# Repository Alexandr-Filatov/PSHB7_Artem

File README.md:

# C6_Driver_3
Driver board for C6 IGBT Module.

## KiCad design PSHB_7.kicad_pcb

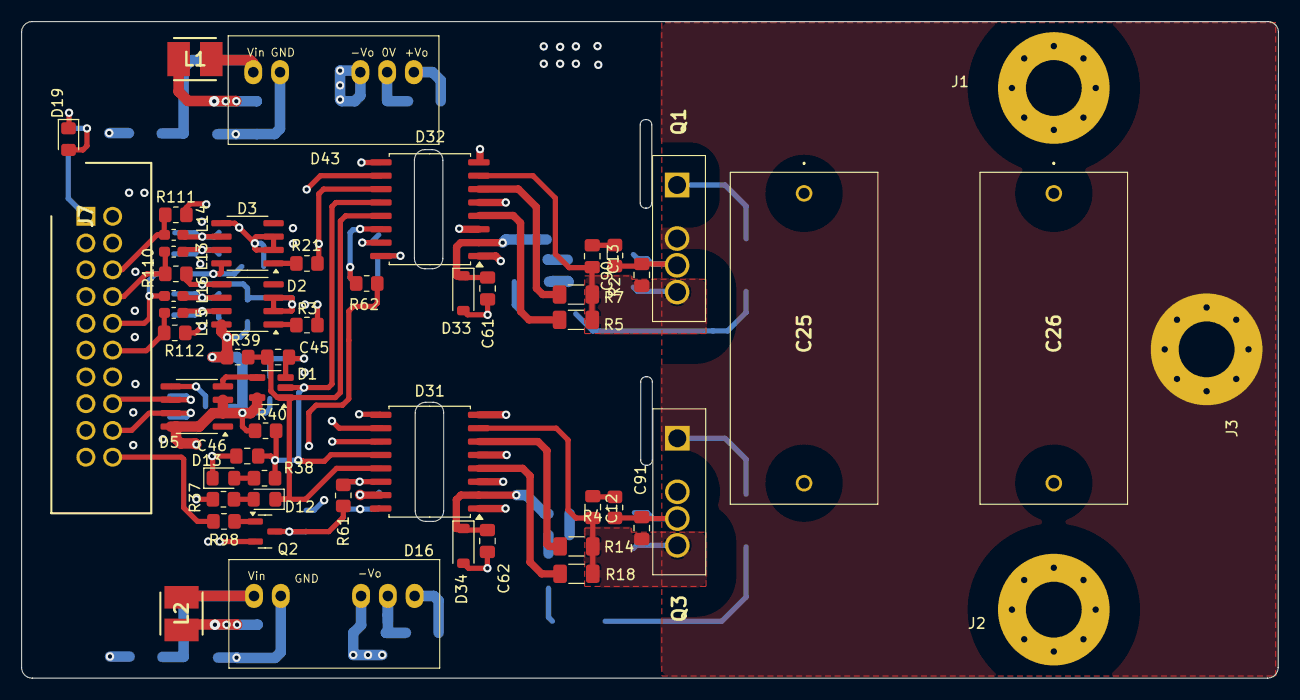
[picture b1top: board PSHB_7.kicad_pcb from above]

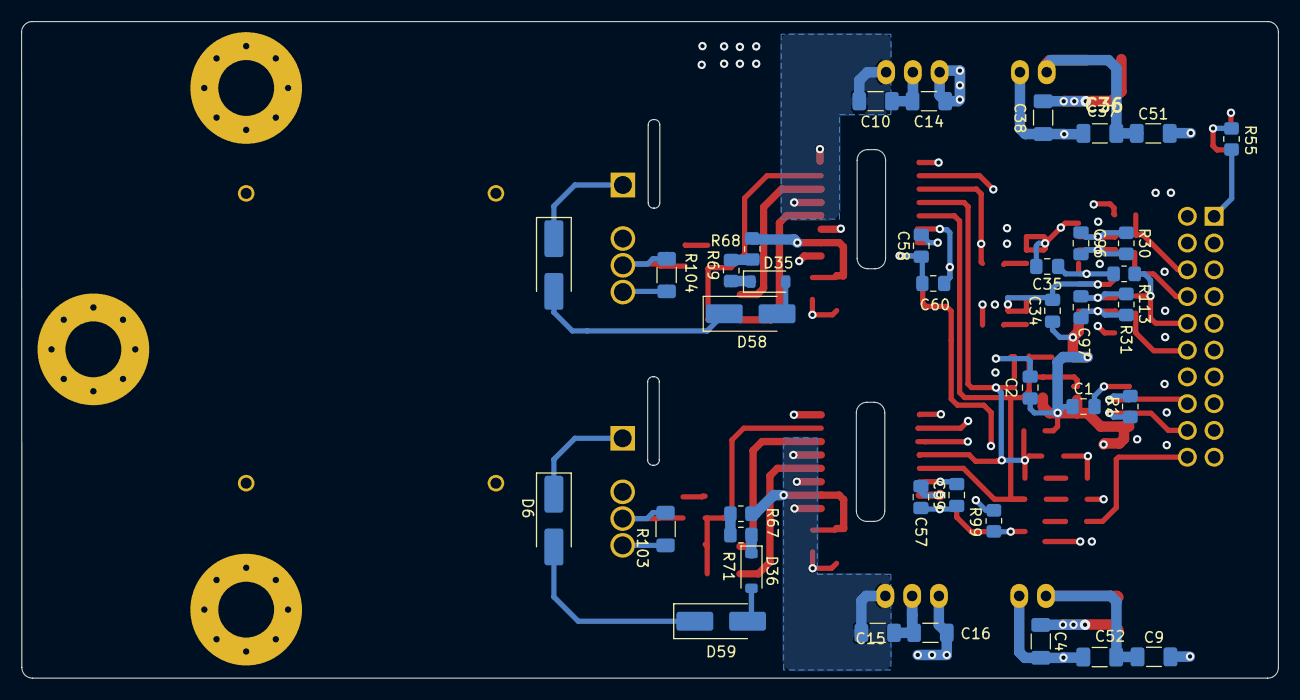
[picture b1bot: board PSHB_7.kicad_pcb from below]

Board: 6 copper layers, 119.3 x 62.3 mm, 92 parts (38 on the bottom side), 55 nets.

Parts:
C1, C2, C34, C35: 2.2u; C_0805_2012Metric_Pad1.18x1.45mm_HandSolder
C4, C9, C37, C38: 4.7u; C_1206_3216Metric_Pad1.33x1.80mm_HandSolder
C10, C14, C15, C16: 10uf; R_1206_3216Metric_Pad1.30x1.75mm_HandSolder
C12, C13: 470p; C_0805_2012Metric_Pad1.18x1.45mm_HandSolder
C25, C26: B32774D8505K000
C45, C46, C96, C97: 56p; C_0805_2012Metric_Pad1.18x1.45mm_HandSolder
C51, C52: 100p; C_1206_3216Metric_Pad1.33x1.80mm_HandSolder
C57, C58: 0.1u; C_0805_2012Metric_Pad1.18x1.45mm_HandSolder
C59, C60: 1000p; C_0805_2012Metric_Pad1.18x1.45mm_HandSolder
C61, C62: 220p; C_0805_2012Metric_Pad1.18x1.45mm_HandSolder
C90, C91: C_0805_2012Metric_Pad1.18x1.45mm_HandSolder
D1: SOT-23-5_HandSoldering
D2, D3, D5: SOIC-8_3.9x4.9mm_P1.27mm
D4, D6, D58, D59: D_SMA_Handsoldering
D12, D13, D19: LED_0805_2012Metric_Pad1.15x1.40mm_HandSolder
D16, D43: QA
D31, D32: SOIC-16W_7.5x10.3mm_P1.27mm
D33, D34, D35, D36: D_SOD-123
J1, J2, J3: MountingHole_5.3mm_M5_Pad_Via
J7: DS1013-20SSIB1-B-0; SHDR20W69P254X254_2X10_3300X910X955P
L1, L2: IFSC1515AHER220M01; INDM4040X190N
L13, L14, L15, L16: 1u; L_0603_1608Metric_Pad1.05x0.95mm_HandSolder
Q1, Q3: C3M0065100K; E4M0013120K
Q2: SOT-23
R1, R30, R31, R61, R62: 120; R_0805_2012Metric_Pad1.20x1.40mm_HandSolder
R2, R4, R37, R38, R39, R40, R99: 1k; R_0805_2012Metric_Pad1.20x1.40mm_HandSolder
R3, R21, R69, R71: 0; R_0805_2012Metric_Pad1.20x1.40mm_HandSolder
R5, R18: 6.8; R_1206_3216Metric_Pad1.30x1.75mm_HandSolder
R7, R14: 10; R_1206_3216Metric_Pad1.30x1.75mm_HandSolder
R55: 3k; R_0805_2012Metric_Pad1.20x1.40mm_HandSolder
R67, R68: 220; R_0805_2012Metric_Pad1.20x1.40mm_HandSolder
R98: 4.7k; R_0805_2012Metric_Pad1.20x1.40mm_HandSolder
R103, R104: 10k; R_1206_3216Metric_Pad1.30x1.75mm_HandSolder
R110, R111, R112, R113: 560; R_0805_2012Metric_Pad1.20x1.40mm_HandSolder

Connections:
+5V: C1.1, C2.1, C34.1, C35.1, C57.2, C58.2, D1.5 (Vcc), D2.8 (VCC), D3.8 (VCC), D5.2 (RE), D5.3 (DE), D5.8 (VCC), D31.15 (Vcc1), D32.15 (Vcc1), J7.4, J7.14, R37.2, R39.2, R40.2, R99.2, R111.2, R113.2
+15V: C4.1, C38.1, J7.1, L1.1, L2.1, R55.2
+15V_H1: C10.1, D32.5 (Vcc2), D43.7 (+Vo)
+15V_L1: C15.1, D16.7 (+Vo), D31.5 (Vcc2)
-4V_H1: C14.2, D32.1 (Vee2), D32.8 (Vee2), D43.5 (-Vo)
-4V_L1: C16.2, D16.5 (-Vo), D31.1 (Vee2), D31.8 (Vee2)
D1: C25.1, C26.1, D4.1 (K), J1.1 (Pin_1_1), Q1.1 (D)
D2: C10.2, C14.1, C61.2, C90.1, D6.1 (K), D32.3 (GND2), D33.2 (A), D43.6 (0V), J3.1 (Pin_1_1), Q1.2 (S), Q1.3 (DS), Q3.1 (D), R2.1, R104.1
DS2: C15.2, C16.1, C25.2, C26.2, C62.2, C91.1, D16.6 (0V), D31.3 (GND2), D34.2 (A), J2.1 (Pin_1_1), Q3.2 (S), Q3.3 (DS), R4.1, R103.1
ERR_A_N: D5.7 (B), J7.18, R1.1
ERR_A_P: D5.6 (A), J7.16, R1.2
FLT_A: C45.1, D1.1 (B), D12.1 (K), D31.13 (~FLT), D32.13 (~FLT), R39.1
G1: C13.1, C90.2, D32.7 (CLAMP), Q1.4 (G), R5.1, R7.2, R104.2
G2: C12.1, C91.2, D31.7 (CLAMP), Q3.4 (G), R14.2, R18.1, R103.2
GND: C1.2, C2.2, C4.2, C9.2, C34.2, C35.2, C37.2, C38.2, C45.2, C46.2, C51.2, C52.2, C57.1, C58.1, C59.1, C60.1, D1.3 (GND), D2.2 (RE), D2.3 (DE), D2.5 (GND), D3.2 (RE), D3.3 (DE), D3.5 (GND), D5.5 (GND), D13.1 (K), D16.2 (GND), D19.1 (K), D31.9 (GND1), D31.16 (TEST), D32.9 (GND1), D32.16 (TEST), D43.2 (GND), J7.2, J7.3, J7.5, J7.7, J7.9, J7.11, J7.13, J7.15, J7.17, J7.19, Q2.2 (E), R110.1, R112.1
IN-_HS: D31.10 (IN+), D32.11 (IN-), R21.2
IN-_LS: D31.11 (IN-), D32.10 (IN+), R3.2
unnamed: C12.2, R4.2
unnamed: C13.2, R2.2
unnamed: D1.4 (Y), D5.4 (DI)
unnamed: C97.1, D2.6 (A), L16.1, R31.2
unnamed: C97.2, D2.7 (B), L15.2, R31.1
unnamed: C96.1, D3.6 (A), L14.1, R30.2
unnamed: C96.2, D3.7 (B), L13.2, R30.1
unnamed: D4.2 (A), D58.1 (K)
unnamed: D12.2 (A), R37.1
unnamed: D13.2 (A), R38.1
unnamed: C9.1, C52.1, D16.1 (Vin), L2.2
unnamed: D19.2 (A), R55.1
unnamed: C62.1, D31.2 (DESAT), D34.1 (K), R67.2
unnamed: D31.4 (OUTH), R18.2
unnamed: D31.6 (OUTL), R14.1
unnamed: C59.2, D31.14 (~RST), R61.2
unnamed: C61.1, D32.2 (DESAT), D33.1 (K), R68.2
unnamed: D32.4 (OUTH), R5.2
unnamed: D32.6 (OUTL), R7.1
unnamed: C60.2, D32.14 (~RST), R62.2
unnamed: D35.2 (A), D58.2 (A)
unnamed: D35.1 (K), R69.1
unnamed: D36.2 (A), D59.2 (A)
unnamed: D36.1 (K), R71.1
unnamed: C37.1, C51.1, D43.1 (Vin), L1.2
unnamed: D6.2 (A), D59.1 (K)
unnamed: Q2.1 (B), R98.2
unnamed: R67.1, R71.2
unnamed: R68.1, R69.2
PWM1_H_N: J7.12, L15.1, R112.2
PWM1_H_P: J7.10, L16.2, R113.1
PWM1_L_N: J7.8, L13.1, R110.2
PWM1_L_P: J7.6, L14.2, R111.1
PWM_H1: D2.1 (RO), R3.1
PWM_L1: D3.1 (RO), R21.1
RDY_A: C46.1, D1.2 (A), D31.12 (RDY), D32.12 (RDY), R38.2, R40.1
~RST_A: Q2.3 (C), R61.1, R62.1, R99.1
~RST: J7.20, R98.1

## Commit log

2026-05-20 Поменял десат подключение, сделал зазоры на силовых полигонах
